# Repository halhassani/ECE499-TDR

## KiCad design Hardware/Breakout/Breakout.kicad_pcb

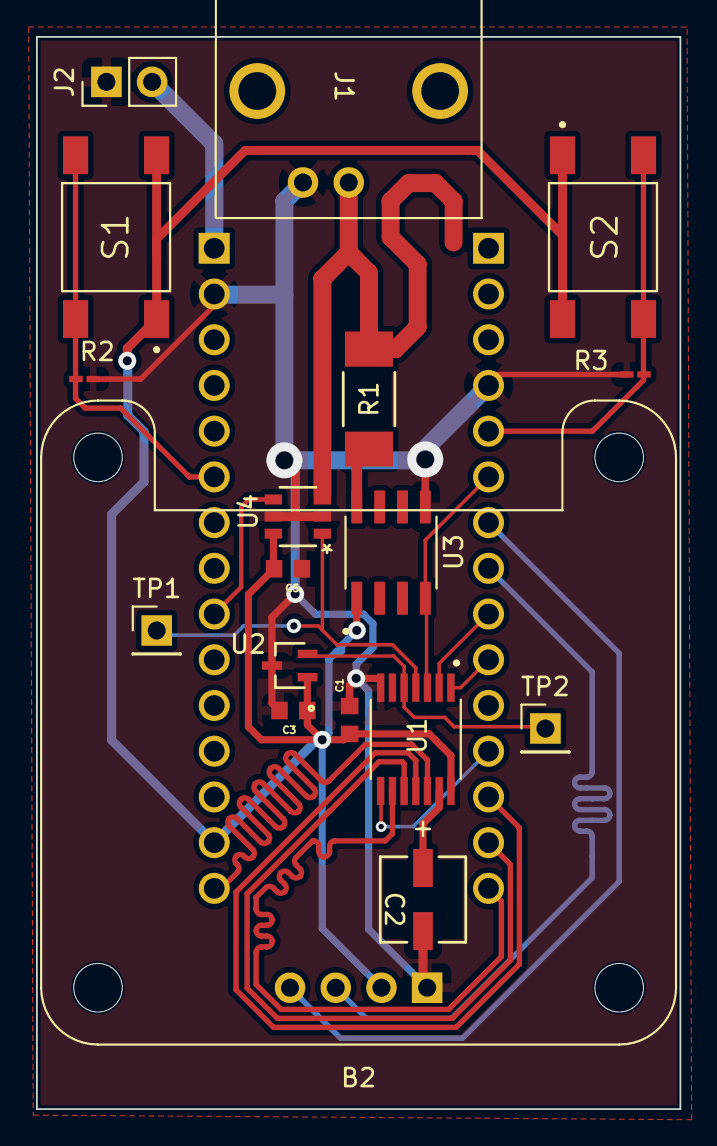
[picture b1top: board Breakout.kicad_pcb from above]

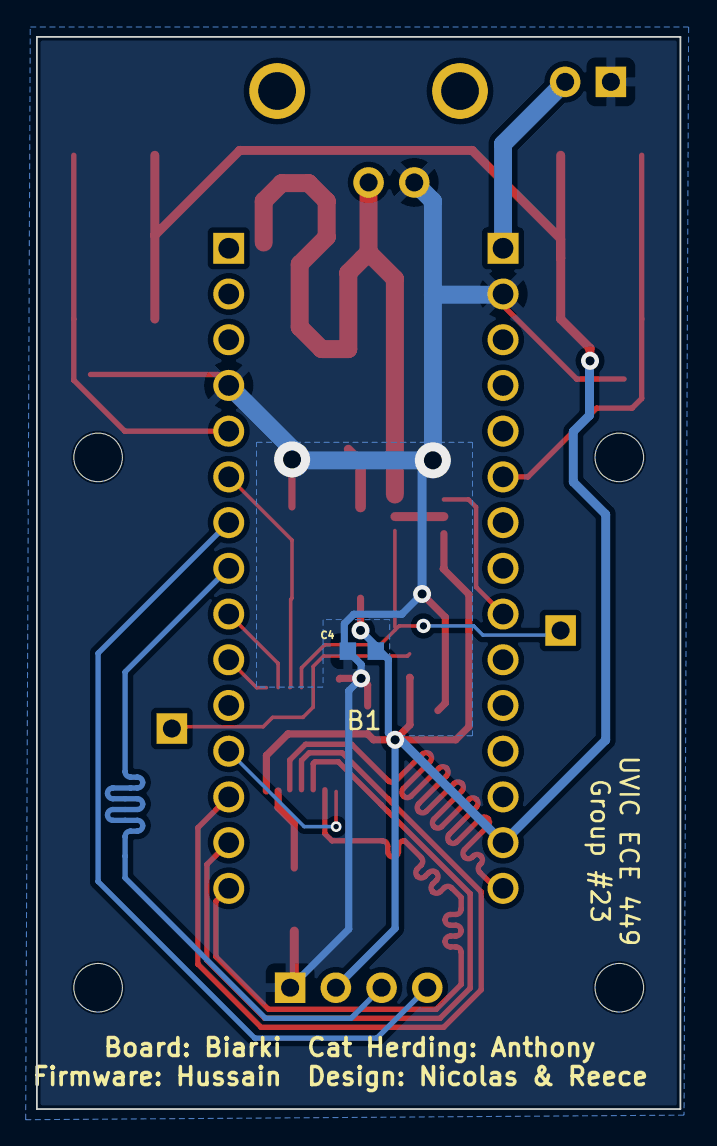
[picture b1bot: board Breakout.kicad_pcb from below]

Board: 2 copper layers, 35.8 x 59.6 mm, 20 parts (2 on the bottom side), 21 nets.

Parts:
B1: NUCLEO-G431KB; DIPS1524W66P254L5029H1500Q30N
B2: SSD1306; Adafruit_SSD1306_4Pin
C1, C3, C4, C5: 0.1uF; CAPC1608X90N
C2: 1uF; PCAP_4x5.4-ELECT_NCA-L
J1: Conn_Coaxial; 0731375003_BCN_conn
J2: 9v_batt_in; PinHeader_1x02_P2.54mm_Vertical
R1: 50R; RES_WSC_2515-M
R2, R3: 100k; RC0201N_VIS-M
S1, S2: TL3301PF160QG; SW_TL3301PF160QG
TP1, TP2: TestPoint; PinHeader_1x01_P2.54mm_Vertical
U1: TDC7200PWR; SOP65P640X120-14N
U2: MAX7375AXR805+T; 21-0075D_MXM
U3: BUF602ID; SOIC127P600X175-8N
U4: MAX9011EUT+T; 21-0058I_MXM

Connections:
+3.3V: B1.17 (+3V3), B2.2 (VCC), C1.1, C3.1, C4.2, C5.2, S1.1, S1.2, S2.1, S2.2, U1.14 (VDD), U2.1 (V+), U3.1 (VCC+), U4.6 (VCC)
+9V: B1.30 (VIN), J2.2
Button 1: B1.25 (PA7(A6)), R2.1, S1.3, S1.4
Button 2: B1.5 (PA12(D2)), R3.1, S2.3, S2.4
DACPin: B1.22 (PA4(A3)), U4.4 (IN-)
GND: B1.4 (GND@1), B1.29 (GND@2), B2.1 (GND), C1.2, C2.2, C3.2, C4.1, C5.1, J1.2 (Ext), J2.1, R2.2, R3.2, U1.7 (GND), U2.3 (GND), U3.5 (VCC-), U4.2 (GND), U4.5 (LE)
MISO: B1.15 (PB4(D12)), U1.9 (DOUT)
MOSI: B1.14 (PB5(D11)), U1.10 (DIN)
unnamed: J1.1 (In), R1.2, U4.3 (IN+)
unnamed: C2.1, U1.13 (VREG)
unnamed: R1.1, U3.8 (OUT)
PULSESIG: B1.6 (PB0(D3)), U1.3 (START), U3.4 (IN)
REFCLK: TP2.1, U1.5 (CLOCK), U2.2 (CLOCK)
SCL: B1.8 (PA15(D5)), B2.3 (SCL)
SDA: B1.7 (PB7(D4)), B2.4 (SDA)
SPICLK: B1.16 (PB3(D13)), U1.12 (SCLK)
STOP: TP1.1, U1.4 (STOP), U4.1 (OUT)
TDCEN: B1.10 (PF0(D7)), U1.1 (ENABLE)
TDCINTERRUPT: B1.12 (PA8(D9)), U1.8 (INT_N)
TDCTRIG: B1.9 (PB6(D6)), U1.2 (TRIGG)
TDC_CS: B1.13 (PA11(D10)), U1.11 (CS_N)

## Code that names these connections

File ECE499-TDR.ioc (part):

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Mcu.Name=STM32G431K(6-8-B)Tx
Mcu.Package=LQFP32
Mcu.UserName=STM32G431KBTx
PA11.GPIOParameters=GPIO_Speed,PinState,GPIO_PuPd,GPIO_Label
PA11.GPIO_Label=TDC7200_CS
PA11.GPIO_PuPd=GPIO_PULLUP
PA11.GPIO_Speed=GPIO_SPEED_FREQ_HIGH
PA11.PinState=GPIO_PIN_SET
PA11.Signal=GPIO_Output
PA12.GPIOParameters=GPIO_Label
PA12.GPIO_Label=BUTTON2
PA12.Signal=GPIO_Input
PA13.Mode=Serial_Wire
PA13.Signal=SYS_JTMS-SWDIO
PA14.Mode=Serial_Wire
PA14.Signal=SYS_JTCK-SWCLK
PA15.Mode=I2C
PA15.Signal=I2C1_SCL
PA4.Signal=COMP_DAC11_group
PA7.GPIOParameters=GPIO_Label
PA7.GPIO_Label=BUTTON1
PA7.Signal=GPIO_Input
PA8.GPIOParameters=GPIO_Label,GPIO_ModeDefaultEXTI
PA8.GPIO_Label=TDC7200_INT
PA8.GPIO_ModeDefaultEXTI=GPIO_MODE_IT_RISING_FALLING
PA8.Signal=GPXTI8
PA9.GPIOParameters=GPIO_Speed,GPIO_Label
PA9.GPIO_Label=ADXL345
PA9.GPIO_Speed=GPIO_SPEED_FREQ_HIGH
PA9.Signal=GPIO_Output
PB0.GPIOParameters=GPIO_Label
PB0.GPIO_Label=PULSE_SIG
PB0.Signal=GPIO_Output
PB3.GPIOParameters=GPIO_Speed
PB3.GPIO_Speed=GPIO_SPEED_FREQ_HIGH
PB3.Mode=Full_Duplex_Master
PB3.Signal=SPI1_SCK
PB4.GPIOParameters=GPIO_Speed
PB4.GPIO_Speed=GPIO_SPEED_FREQ_HIGH
PB4.Mode=Full_Duplex_Master
PB4.Signal=SPI1_MISO
PB5.GPIOParameters=GPIO_Speed
PB5.GPIO_Speed=GPIO_SPEED_FREQ_HIGH
PB5.Mode=Full_Duplex_Master
PB5.Signal=SPI1_MOSI
PB6.GPIOParameters=GPIO_Label,GPIO_ModeDefaultEXTI
PB6.GPIO_Label=TDC7200_TRIG
PB6.GPIO_ModeDefaultEXTI=GPIO_MODE_IT_RISING
PB6.Signal=GPXTI6
PB7.Mode=I2C
PB7.Signal=I2C1_SDA
PF0-OSC_IN.GPIOParameters=GPIO_Speed,PinState,GPIO_PuPd,GPIO_Label
PF0-OSC_IN.GPIO_Label=TDC7200_EN
PF0-OSC_IN.GPIO_PuPd=GPIO_NOPULL
PF0-OSC_IN.GPIO_Speed=GPIO_SPEED_FREQ_HIGH
PF0-OSC_IN.PinState=GPIO_PIN_RESET
PF0-OSC_IN.Signal=GPIO_Output
RCC.HSE_VALUE=25000000
RCC.SYSCLKFreq_VALUE=160000000
RCC.SYSCLKSource=RCC_SYSCLKSOURCE_PLLCLK
board=NUCLEO-G431KB
boardIOC=true

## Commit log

2023-06-18 1 ADC Setup Normal Mode
    yus
2023-06-18 built project - no juice
    yus
2023-06-18 Working ADC, DAC and DMA
    yus
2023-06-18 ADC1 - Continuous Mode enabled
    ADC clock prescaler to 16
    Purpose: to make ADC run as fast as possible in this "bulb mode" where the ADC multiplexer does not change channels (continuous mode) resulting in no delay/noise from ADC mux since it aint moving bru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
2023-06-18 Changed from TIM1,2 to TIM6,7 (much lower pwr)
    TIM6,7 are basic timers and consume 1/5 the amount of current than TIM1,2
    Yus: STM32G431KB Datasheet page 94
2023-06-18 TIM1,2 changed to TIM6,7 in main.c code
    Yus
2023-06-18 Set all unused GPIO pins to ANALOG mode (save pwr)
    Yus. Reduce current consumption from unused GPIO pins (which are default as DIGITAL) -> set to ANALOG
    Yus
2023-06-18 Print ADC value from DMA save location
    Yus.
    Changed from using ADC_GetValue function to just printing the ADC values from the variable which was passed to the ADC_DMA function.
    Removes redundancy and improves optimization ong fr fr no cap.
2023-06-18 Cleaned up main.c juicer
    Yus
2023-06-18 Reformatted main.c - autoformat
    Yus.
2023-06-19 Tested DAC at 10MHz sampling rate
    Yus.
    ie: changed TIM6 to trigger every 10MHz since DAC samples at every TIM6 event trigger
2023-06-19 Change CPU Clk to 120MHz, made ADC optimal sampling rate
    Yus.
    Datasheet says ADC max sampling rate occurs at 60MHz ADC clk rate, so i changed CPU clk rate accordingly
    Yus.
2023-06-20 Enabled TIM15 (triggers event every 4MHz)
    Yus
2023-06-20 Added OLED graphics for some testing
    Yus.
2023-06-20 Start TIM15 -> triggers ADC bruh
    Yus
2023-06-20 Changed ADC and timer parameters
    Played around with different configurations and observed sampling rate changes on Logic Analyzer
    Yus.
2023-06-21 ADC interleaved w/ LogicAnalyzer
    Juice.
2023-06-22 Playing around with ADC Interleaved & TIM3-OC
    Observing ADC sampling rate by making the triggering timer TIM3 output a pulse on the OutputComparitor pin, -> viewing that on the Logic Analyzer
    (Works gucci)
2023-06-23 More Logic Analyzer Timings for ADC, DAC, HW TIMs
    yus
2023-06-23 Switched from TIM15 to TIM3 for OC, CH1
    yus.
    Output comparator CH1 for TIM3 used for debugging bruh ong fr fr
2023-06-23 ADC triggers on rising&falling edge of TIM3
    yus
2023-06-23 TIM3 Output Comparitor Debugging Works
    Had to change DMA buffer from Circular to Normal..............
    Now I can confirm that ADC is being triggered every 4MHz by TIM3
2023-06-24 Updated STM32CubeIDE to newest version
    Yus.
2023-06-24 Updated STM32CubeIDE Software to newest juicer
    yus
2023-06-26 Setup TIM2 DMA trigger juicer
    yus
2023-06-27 Changed SystemClk to 170MHz
    Yus
2023-06-27 Changed HSE input freq to 25 MHz (prev 48MHz)
    Yus. RCC HSE clock with previous parameters was giving error in clock configuration code, datasheet says HSE bypass oscillator is 25MHz, not 48MHz or anything else. Yus
2023-06-27 Disabled HSE oscillator options, used HSI: 170MHz
    Turns out all HSE oscillator clocks arent even electrically connected to the MCU!!!! (They are present on the PCB but require solder bridges to enable them...) Reverted back to HSI internal clock fro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
2023-06-27 TIM2 (DMA Trig timer) OC set back to toggle
    Yus. Tested "Active Level on Match" OC pin but that results in logic HIGH on TIM2 pin PA5.. no change after the first match. Reverted back to "Toggle on Match" for debugging purposes
2023-06-27 Fixed all Timer prescalers (ST req's PSC-1)
    yus
2023-06-27 TIM2 set to 10MHz (DMA trigger)
    yus
2023-06-27 TIM2 set to 17 MHz (DAC trig)
    yus
2023-06-27 TIM2 set to ~24 MHz (DAC trig)
    yus
2023-06-27 TIM2 set to 34 MHz (DAC trig)
    yus
2023-06-27 ADC disables Cont.Conv.Mode
    Yus. Timer TIM3 event triggers cause ADC to sample at specified frequency (TIM3 currently set to 2 MHz)
2023-06-27 SysCLK 170MHz, TIMx's changed, ADC dual mode
    yus. Baseline debugging juicer
2023-06-27 Enabled TIM2 and TIM2_OC for debug DMA juicer
    yus
2023-06-27 DAC trigger (TIM7) set to 1MHz
    yus
2023-06-27 TIM7 1MHz
2023-06-27 TIM7 (DAC trig) 2MHz juicer
    yus
2023-06-29 Added data sheet and extra file structure to test git push
2023-07-02 Began KiCAD Project
2023-07-03 Added few parts
2023-07-04 Baseline Code
    Yus
2023-07-04 ADXL345 Library Header definitions
    Ong fr fr yus
2023-07-04 Implemented ADXL Driver Functions in source file
    Yus.
2023-07-04 Fully Functioning ADXL library driver
    Yus. Juice ong fr fr
2023-07-04 Baseline Code for TDC7200 Driver Files
    Yus.
2023-07-04 TDC7200 Header File Register Map Defines
    Yus. These are all of the relevant registers that are present on this IC. We use these registers to configure the TDC accordingly.
2023-07-05 Added TDC circiut to main schem, still need to make sure its all hoodked up right
2023-07-05 File-Corrected Commit: TDR2700.h/c
    Yus.
2023-07-05 TDC7200 Driver Function Prototype Declarations
    Yus.
2023-07-05 SPI1 peripheral enabled
    Yus
2023-07-05 Began PCB layout
2023-07-06 TDC7200 Driver functions
2023-07-06 ADXL Driver now includes SPI (practicing SPI driver development)
    Yus. Will use for reference if i get stuck on writing SPI-capable driver for TDC7200 chip. Ong fr fr
2023-07-07 Upload of hardware changes as of 6pm 06/07/2023
2023-07-07 Further TDC SPI Driver Improvements
    Yus.
    Completed fxn that allows us to write to any TDC register.
    Included TDC-specific SPI command bits (read/write, auto-increment). Big juice
    Yus.
2023-07-07 TDC7200 Driver Header file: Register Struct TypeDefs
    Yus.
    Register struct typedefs will make low-level register configurations easier, faster.
    ~~ABSTRACTION~~
    Yus.
2023-07-07 TDC7200 More Driver Abstraction Code for Driver File
    Yus.
    Makes register bitfields a lot easier to access. Results in more readable code when the user wants to configure various bits in different registers.
    Yus.
2023-07-07 Buttons and fine turning still required
2023-07-07 TDC: Bitfield defines for a few registers
    Yus.
2023-07-07 Almost final board, need to fix silkscreen
2023-07-07 adjusted IC footprints, DRC massaging, added test points, added 9v input pins,
2023-07-07 sanity check commit to make sure changes are saved
2023-07-08 Updated All Pinouts to match PCB Schematic
    Yus.
2023-07-08 TDC7200 Driver header file: Complete
    Yus.
    Added all relevant register addresses and bitfield macro definitions. Comments gucci
    Yus.
2023-07-08 Unchanged from prev commit, just built project
    Yus.
    Random "under the hood" file changes when I build project. No changes to any code at all.
    Yus.
2023-07-08 fixed DAC pin
2023-07-08 final DRC for JLCPCB
2023-07-11 More revisions and generated Gerbers
2023-07-19 TDC Driver: Read Registers fxn completed
    Yus.
    Can read 1 or multiple registers using 1 fxn.
    This fxn handles the read cmd bit and auto incr. cmd bit when req'd.
    Yus.
2023-07-20 Testing FW with TDC board
    Yus.
    Testing juicer, no response from TDC on SPI line yet when MCU requests data from it.
    Yus.
2023-07-20 Debugging TDC CS pin -> juicer responding (good)
    Yus.
    Slowly but surely climbing up the debugging ladder. Checking every nook and cranny of the code before pointing the finger at the hardware juicer.
    Also changed TDC CS GPIO pin on startup to be logic HIGH (since logic LOW tells SPI to select the TDC immediately for transmission/reception. Start with CS = 1 since TDC wont be selected to talk on S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
    Yus.
2023-07-21 TEST TEST TEST TIETSING TDC JUICER - STILL NO MISO
    Bruh..this TDC chip is a mute ong fr fr.
    Tested various SPI modes (mode 0, 1..etc), tested with SPI motorolla and SPI TI modes. No juice.
    SPI peripheral works fine but receiving any data from TDC no gucci yet.
    Tried raising and lowering SPI baud rate, no juice.
    Updated GPIO pins to match PCB schematic (only TDC interrupt pin was mismatched but nbd)
2023-07-22 MORE TESTING, STILL NO JUICE
    Yus.
    Confirmed again all GPIO pins used to connect TDC to MCU all gucci (TDC_EN, TDC_CS, TDC_INT pins etc), configured correctly.
    Tested more SPI configurations, no juice on MISO line, TDC no talk.
    Yus.
2023-07-22 JUICER WORKING
    yus
2023-07-22 nadda
    yus
2023-07-23 CREATING TDC INIT FXNS, CLEANING UP CODE
    YUS.
    GOOD. MADE TDC INITIALIZATION FXN WHICH HANDLES ALL OF THE REGISTER CONFIGURATIONS THAT WE WANT THE TDC TO HAVE SET.
    CREATED TDC MEASUREMENT FXN WHICH HANDLES THE LOW LEVEL SPI-TX DATA TO TDC JUICER. SO IT IS ABSTRACTED AWAY FROM USERS, JUST USE THIS FXN AND EZ PZ, TDC GIVES JUICER MEASUREMENT.
    YUS.
2023-07-23 Verifying that TDC sets Reg data as commanded (YES)
    Yus.
    TDC Juicer works. I set various registers with certain bit configurations then read those registers back to confirm if values were set, and boom yes gucci. TDC listens, big.
    Yus.
2023-07-23 CHANGED TDC_TRIG PIN ON MCU TO BE AN EXTI PIN
    YUS.
    THIS PIN USE TO BE A NORMAL GPIO INPUT PIN USED TO POLL THE TDC_TRIG PIN BUT DATASHEET SAYS NO POLL ON TDC_TRIG PIN, MESSES UP TDC CALCULATIONS.
    SO I AM CHANGING THIS PIN TO BE AN EXTERNAL INTERRUPT JUICER. MCU CODE WILL HANDLE THE ISR WHENEVER TDC_TRIG PIN RAISES AN INTERRUPT FOR MCU JUICER TO SERVICE. THIS TELLS REST OF CODE THAT A NEW MEAS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
    YUS.
2023-07-23 TDC_INT PIN ALSO CHANGED TO EXTERNAL INT INSTEAD OF GPIO INPUT
    JUICER DATASHEET SAYS NO GUCCI FOR POLLING, SO WE OUT HERE USING ISR's ONG FR FR.
2023-07-23 ADDED ISR FLAGS TO HANDLE EXTI's FROM TDC TO MCU
    YUS.
    ALSO CHANGED USER BUTTON2 TO AN EXTI AS WELL SINCE HAVING IT AS A NORMAL GPIO INPUT WAS NO GOOD, IT WOULDNT IMMEDIATELY RESPOND TO USER PUSHING BUTTON CUZ IT SITS IN THE MAIN WHILE LOOP, WAITING FOR 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
    NO GUCCI, SO IT NOW AN EXTERNAL INTERRUPT THAT FIRES WHENEVER USER PUSHES BUTTON. (maybe will change it back to normal GPIO input if this button ISR messes up with TDC measurement calculations on MCU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
    YUS.
2023-07-23 changed BUTTON2 BACK TO GPIO INPUT, NOT EXTI
    YUS.
    BUTTON2 CHANGED BACK TO NORMAL GPIO INPUT, THE CODE HANDLES BUTTON DEBOUNCING AND IF USER HOLDS BUTTON, CODE WILL WAIT UNTIL USER RELEASES IT BEFORE MOVING ON TO TRIGGER TDC AND DO MEASUREMENT CALCUL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
    YUS.
2023-07-23 REORGANIZED MAIN.C FILE - PLACED TDC FXNS INTO TDC_DRIVER_FILES
    YUS.
    CLEAN.
    YUS.
2023-07-23 COMPLETED TDC TIME CALC FXN JUICER
    YUS.
    SEEMS TO BE WORKING, GOOD JUICE COMING OUT OF TDC CALC FUCNTION BASED ON TDC ToF FORMULA FROM DATASHEET.
    YUS.
2023-07-23 TDC CABLE LENGTH FXN DONE - BIG JUICE- CLEAN CODE
    YUS.
    CLEANED UP MAIN WHILE LOOP JUICER, DE-CLUTTERED BY MOVING JUNK TO BOTTOM OF FILE INSIDE A FXN WHICH IS CALLED IN MAIN LOOP, VERY CLEAN, GOOD JUICE.
    TDC CABLE LENGTH FXN PROTOTYPE JUICER DONE, NEED TO GATHER EXPERIMENTAL DATA OF CABLE PROPOGATION AND SUBTRACT OFFSET JUICER TO GET FINE-TUNED, ACCURATE TDR READINGS, ONG NO CAP FR FR
    YUS.
2023-07-23 Debugged code and fixed some Measurement Calc Errros
    Yus.
    Timing calculation adjusted, offsets introduced, fixed a wrong bitshifting juicer that essentially divided our data by 2.
    All gucci.
    Yus.
2023-07-25 Citation
    Yus.
2023-07-28 Added TDC Trig Flag Debugging - Prints to OLED
    Finalized juicer code, worked on demo day. Removed backupJuicer file, yus.
